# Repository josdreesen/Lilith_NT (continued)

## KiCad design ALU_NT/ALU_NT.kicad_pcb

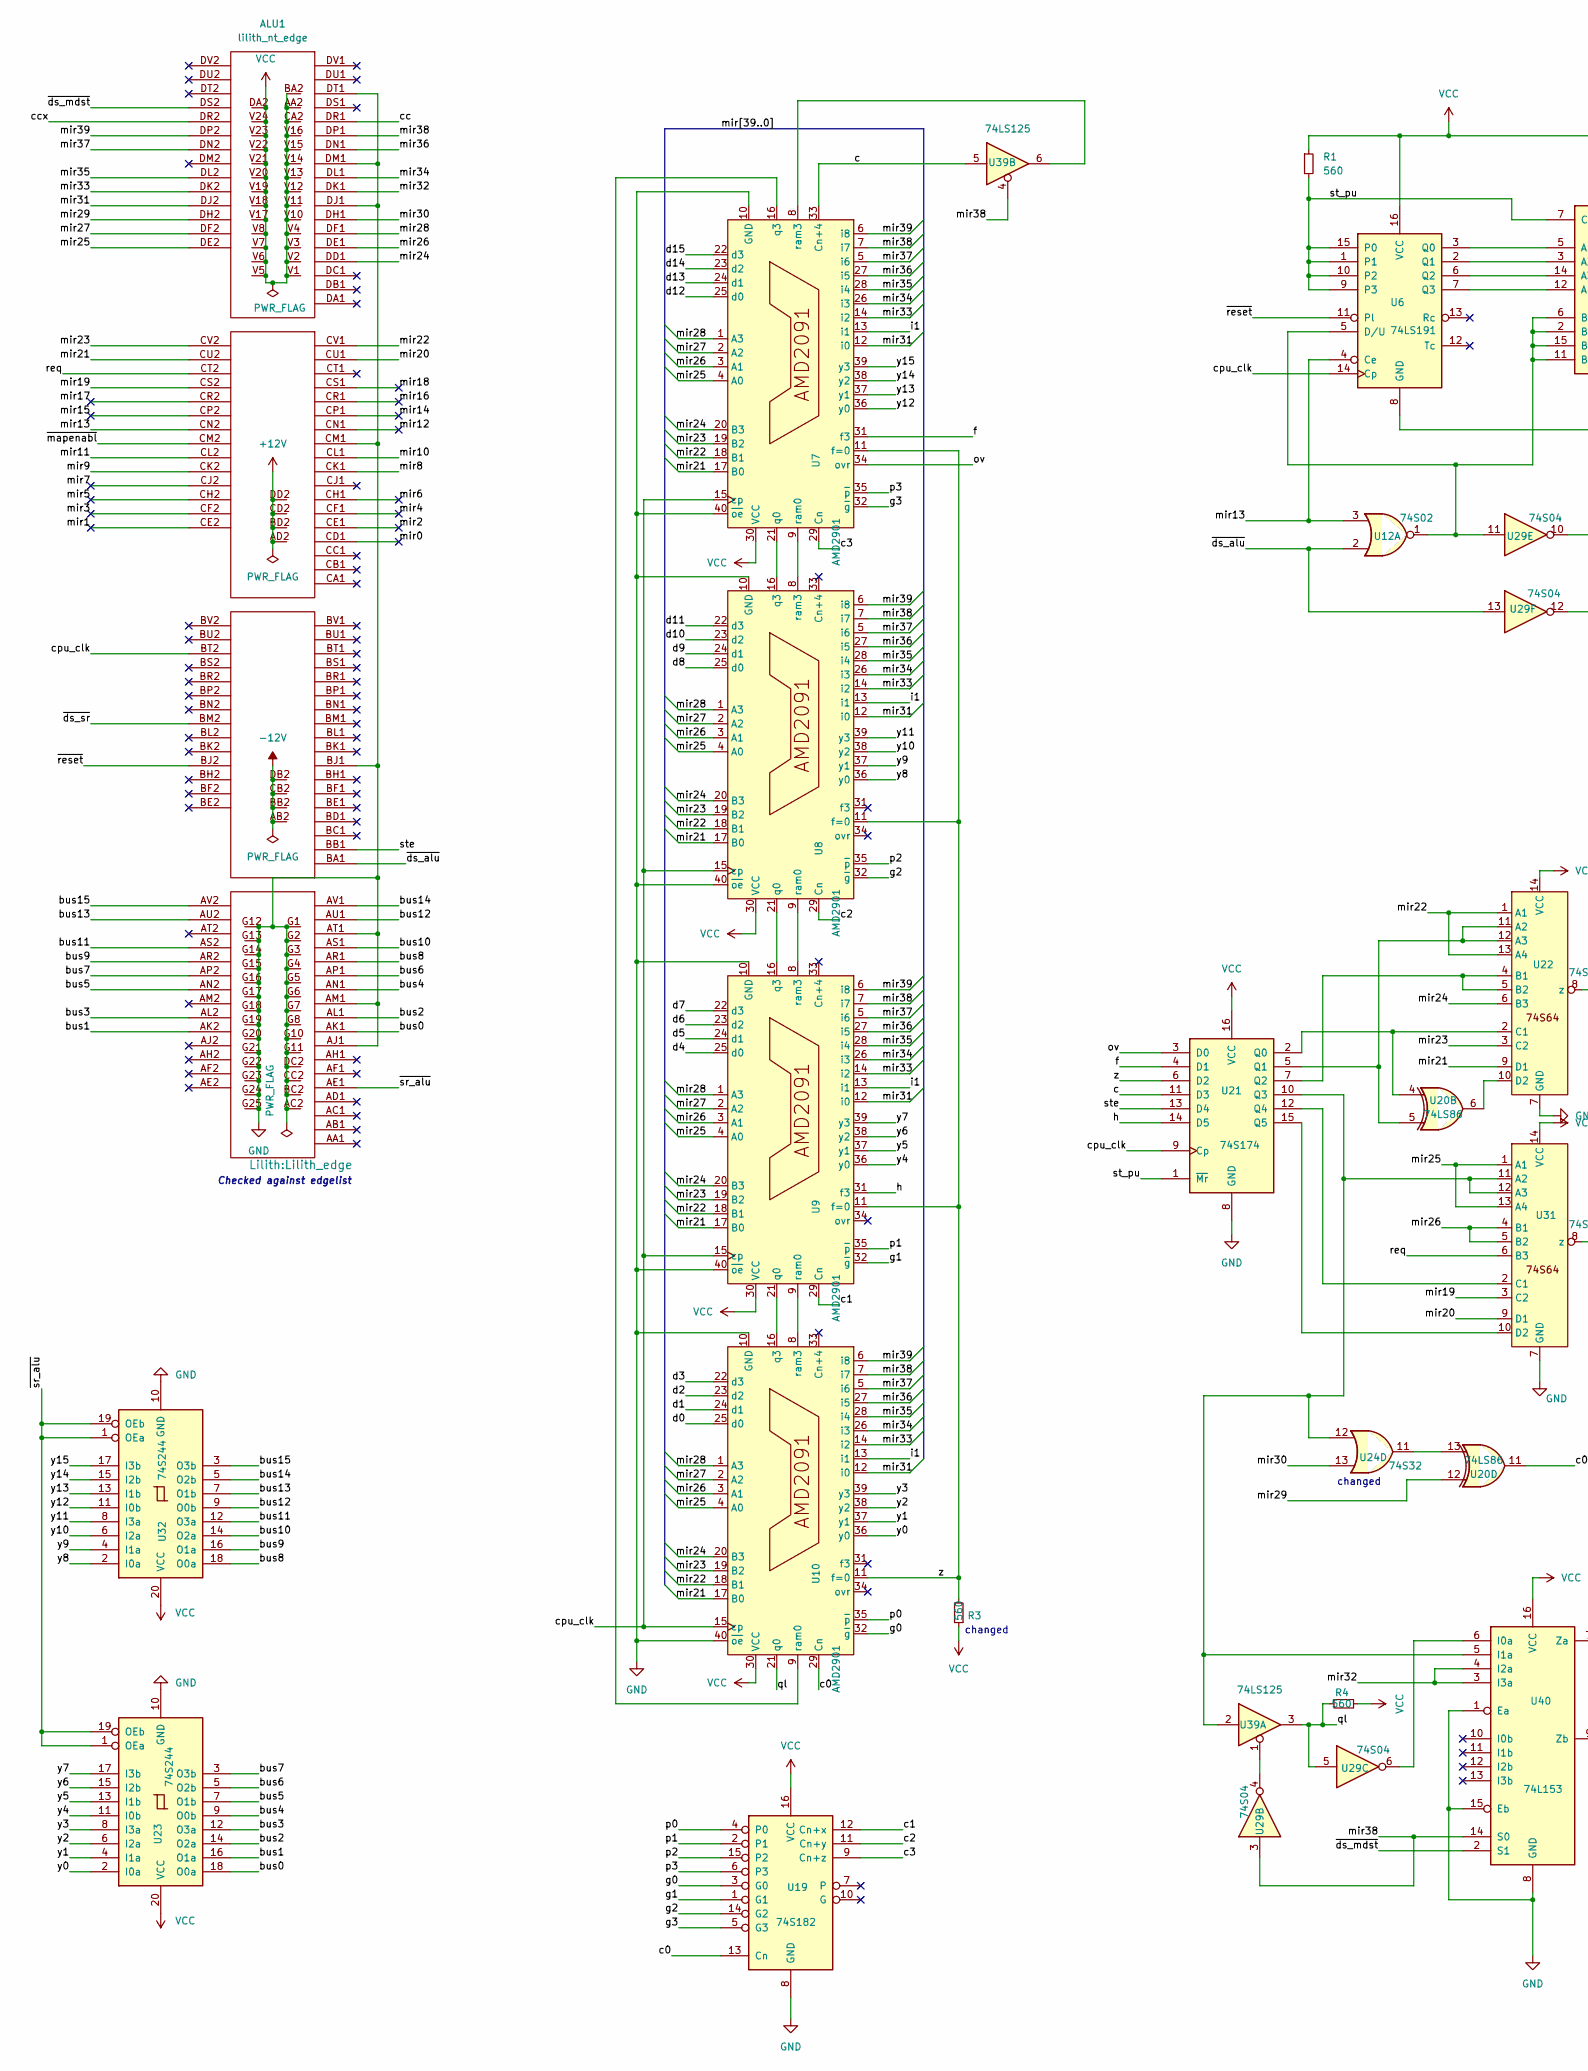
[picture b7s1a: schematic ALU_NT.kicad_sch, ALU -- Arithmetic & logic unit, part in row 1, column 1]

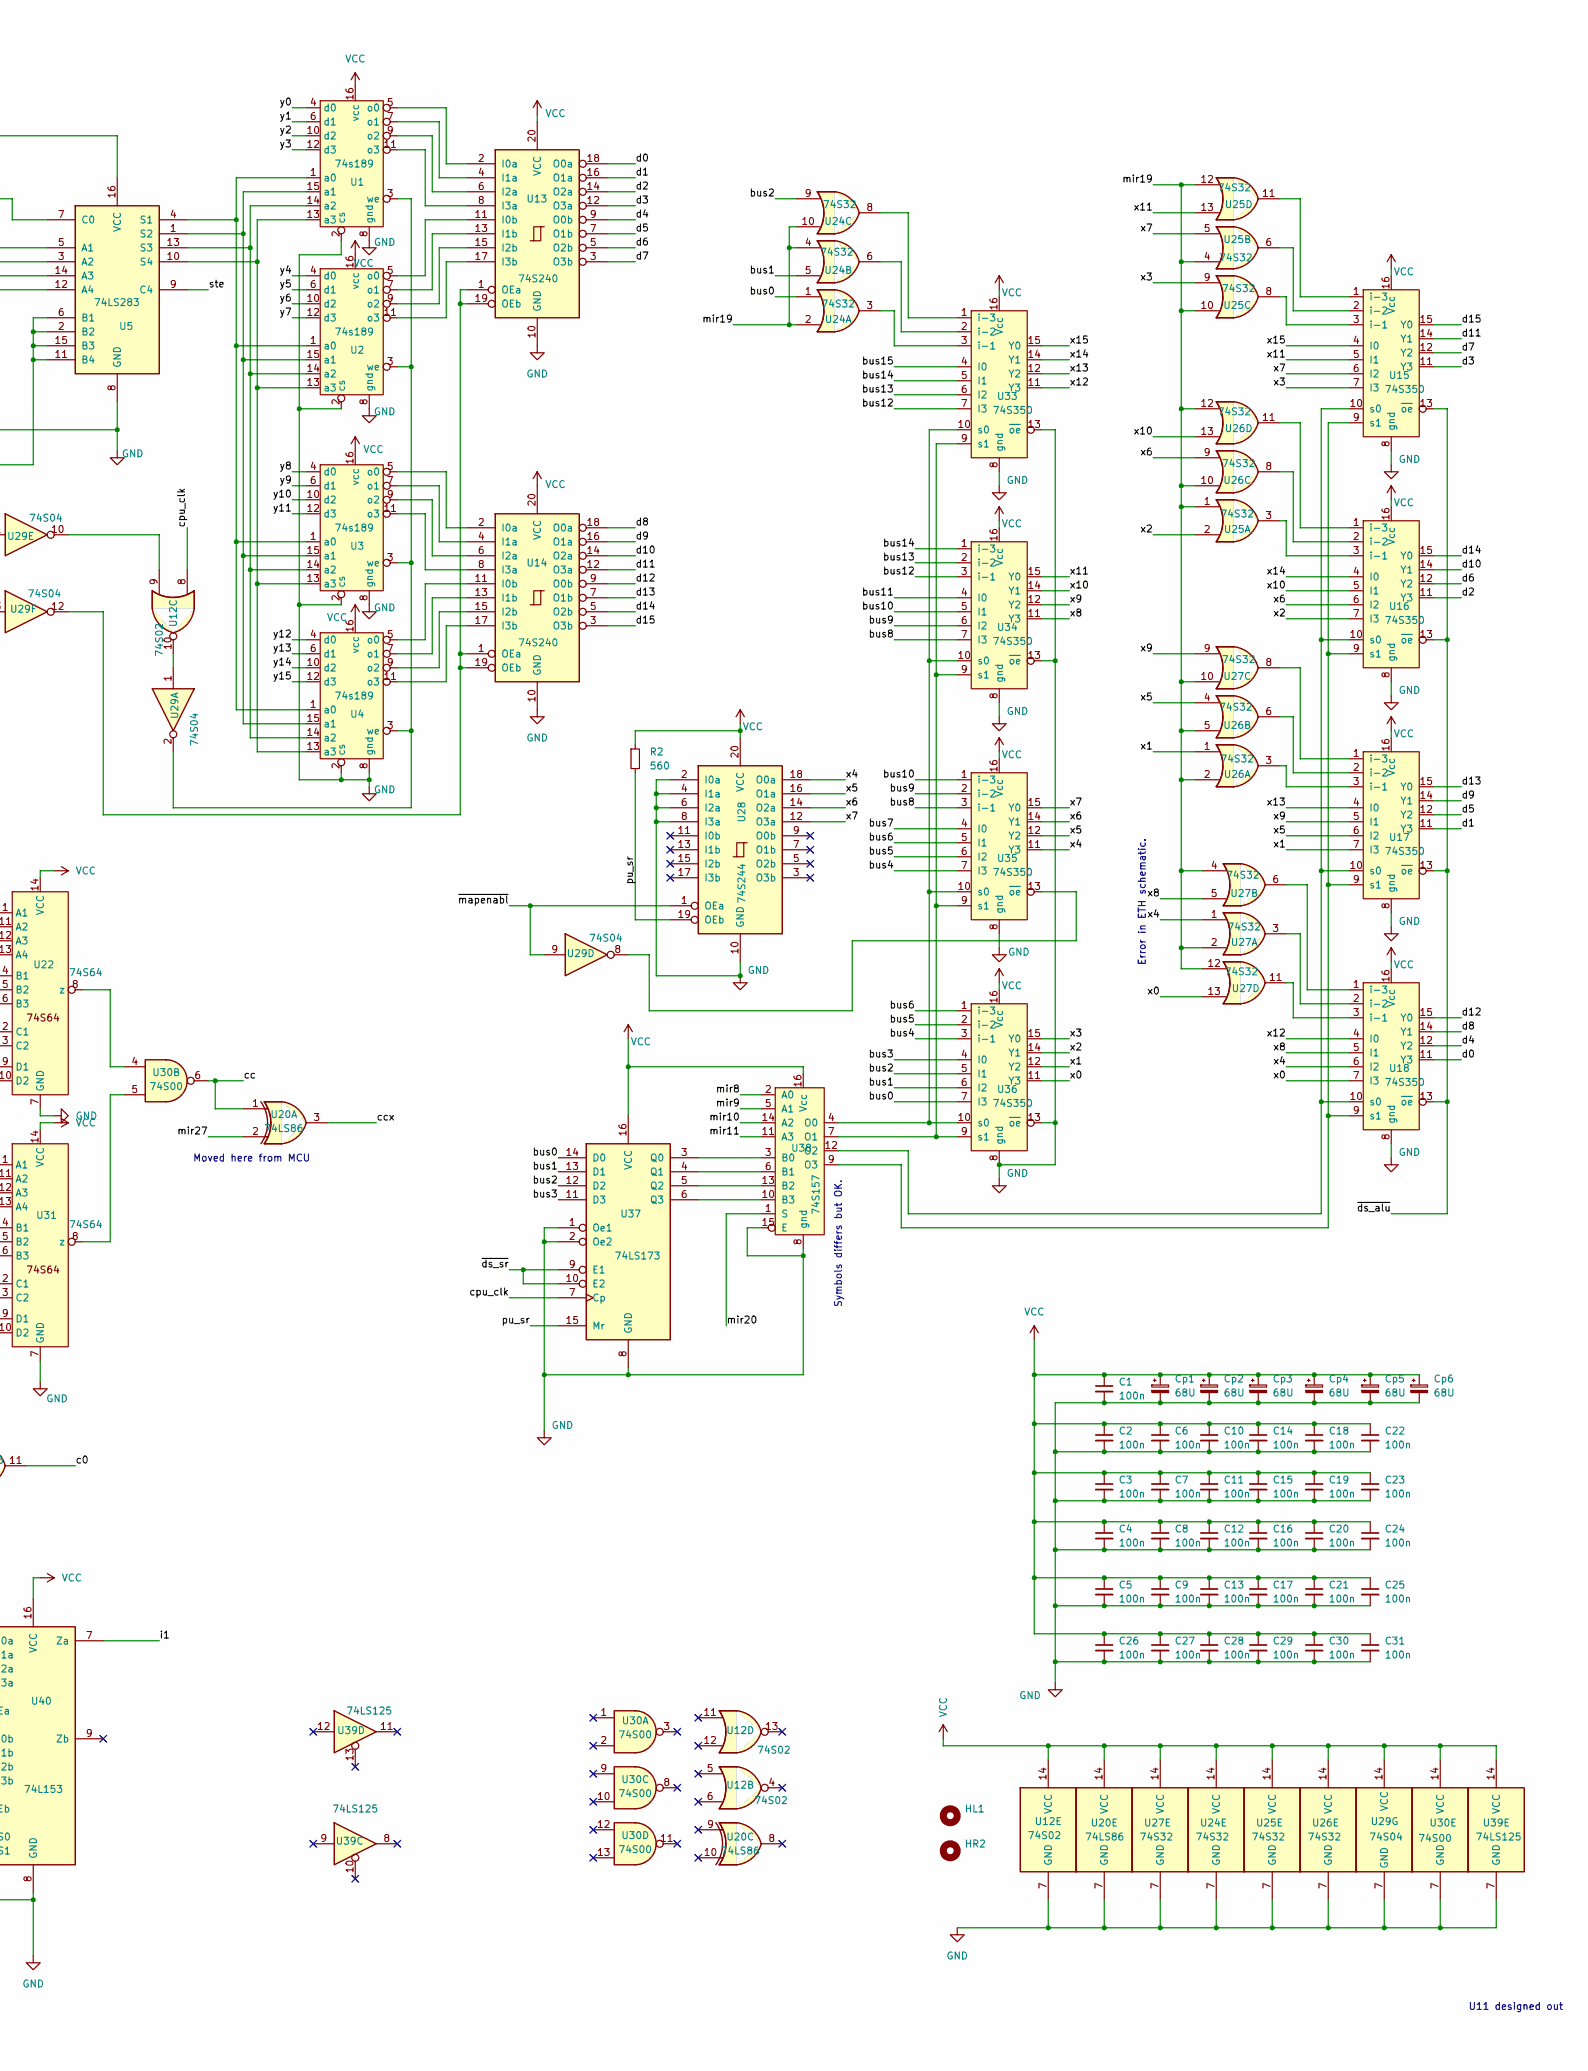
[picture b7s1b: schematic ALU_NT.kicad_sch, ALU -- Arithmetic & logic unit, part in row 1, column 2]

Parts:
ALU1: lilith_nt_edge; Lilith_edge
C1, C2, C3, C4, C5, C6, C7, C8, C9, C10, C11, C12, C13, C14, C15, C16, C17, C18, C19, C20, C21, C22, C23, C24, C25, C26, C27, C28, C29, C30, C31: 100n; C_1206_3216Metric_Pad1.33x1.80mm_HandSolder
Cp1, Cp2, Cp3, Cp4, Cp5, Cp6: 68U; CP_PHP
HL1: MountingHole; Handle
HR2: MountingHole; Handle
R1, R2, R3, R4: 560; R_Axial_DIN0204_L3.6mm_D1.6mm_P7.62mm_Horizontal
U1, U2, U3, U4: 74s189; DIP-16_W7.62mm
U5: 74LS283; DIP-16_W7.62mm
U6: 74LS191; DIP-16_W7.62mm
U7, U8, U9, U10: AMD2901; DIP-40_W15.24mm
U12: 74S02; DIP-14_W7.62mm
U13, U14: 74S240; DIP-20_W7.62mm
U15, U16, U17, U18, U33, U34, U35, U36: 74S350; DIP-16_W7.62mm
U19: 74S182; DIP-16_W7.62mm
U20: 74LS86; DIP-14_W7.62mm
U21: 74S174; DIP-16_W7.62mm
U22, U31: 74S64; DIP-14_W7.62mm
U23, U28, U32: 74S244; DIP-20_W7.62mm
U24, U25, U26, U27: 74S32; DIP-14_W7.62mm
U29: 74S04; DIP-14_W7.62mm
U30: 74S00; DIP-14_W7.62mm
U37: 74LS173; DIP-16_W7.62mm
U38: 74S157; DIP-16_W7.62mm
U39: 74LS125; DIP-14_W7.62mm
U40: 74L153; DIP-16_W7.62mm

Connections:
+12V: ALU1.AD2, ALU1.BD2, ALU1.CD2, ALU1.DD2
-12V: ALU1.AB2, ALU1.BB2, ALU1.CB2, ALU1.DB2
/bus0: ALU1.AK1, U23.18 (O0a), U24.1, U36.7 (I3), U37.14 (D0)
/bus1: ALU1.AK2, U23.16 (O1a), U24.5, U36.6 (I2), U37.13 (D1)
/bus2: ALU1.AL1, U23.14 (O2a), U24.9, U36.5 (I1), U37.12 (D2)
/bus3: ALU1.AL2, U23.12 (O3a), U36.4 (I0), U37.11 (D3)
/bus4: ALU1.AN1, U23.9 (O0b), U35.7 (I3), U36.3 (i-1)
/bus5: ALU1.AN2, U23.7 (O1b), U35.6 (I2), U36.2 (i-2)
/bus6: ALU1.AP1, U23.5 (O2b), U35.5 (I1), U36.1 (i-3)
/bus7: ALU1.AP2, U23.3 (O3b), U35.4 (I0)
/bus8: ALU1.AR1, U32.18 (O0a), U34.7 (I3), U35.3 (i-1)
/bus9: ALU1.AR2, U32.16 (O1a), U34.6 (I2), U35.2 (i-2)
/bus10: ALU1.AS1, U32.14 (O2a), U34.5 (I1), U35.1 (i-3)
/bus11: ALU1.AS2, U32.12 (O3a), U34.4 (I0)
/bus12: ALU1.AU1, U32.9 (O0b), U33.7 (I3), U34.3 (i-1)
/bus13: ALU1.AU2, U32.7 (O1b), U33.6 (I2), U34.2 (i-2)
/bus14: ALU1.AV1, U32.5 (O2b), U33.5 (I1), U34.1 (i-3)
/bus15: ALU1.AV2, U32.3 (O3b), U33.4 (I0)
/c: U7.33 (Cn+4), U21.11 (D3), U39.5
/c0: U10.29 (Cn), U19.13 (Cn), U20.11
/c1: U9.29 (Cn), U19.12 (Cn+x)
/c2: U8.29 (Cn), U19.11 (Cn+y)
/c3: U7.29 (Cn), U19.9 (Cn+z)
/cc: ALU1.DR1, U20.1, U30.6
/ccx: ALU1.DR2, U20.3
/cpu_clk: ALU1.BT2, U6.14 (Cp), U7.15 (cp), U8.15 (cp), U9.15 (cp), U10.15 (cp), U12.8, U21.9 (Cp), U37.7 (Cp)
/d0: U10.25 (d0), U13.18 (O0a), U18.11 (Y3)
/d1: U10.24 (d1), U13.16 (O1a), U17.11 (Y3)
/d2: U10.23 (d2), U13.14 (O2a), U16.11 (Y3)
/d3: U10.22 (d3), U13.12 (O3a), U15.11 (Y3)
/d4: U9.25 (d0), U13.9 (O0b), U18.12 (Y2)
/d5: U9.24 (d1), U13.7 (O1b), U17.12 (Y2)
/d6: U9.23 (d2), U13.5 (O2b), U16.12 (Y2)
/d7: U9.22 (d3), U13.3 (O3b), U15.12 (Y2)
/d8: U8.25 (d0), U14.18 (O0a), U18.14 (Y1)
/d9: U8.24 (d1), U14.16 (O1a), U17.14 (Y1)
/d10: U8.23 (d2), U14.14 (O2a), U16.14 (Y1)
/d11: U8.22 (d3), U14.12 (O3a), U15.14 (Y1)
/d12: U7.25 (d0), U14.9 (O0b), U18.15 (Y0)
/d13: U7.24 (d1), U14.7 (O1b), U17.15 (Y0)
/d14: U7.23 (d2), U14.5 (O2b), U16.15 (Y0)
/d15: U7.22 (d3), U14.3 (O3b), U15.15 (Y0)
/f: U7.31 (f3), U21.4 (D1)
/g0: U10.32 (~g), U19.3 (G0)
/g1: U9.32 (~g), U19.1 (G1)
/g2: U8.32 (~g), U19.14 (G2)
/g3: U7.32 (~g), U19.5 (G3)
/h: U9.31 (f3), U21.14 (D5)
/i1: U7.13 (i1), U8.13 (i1), U9.13 (i1), U10.13 (i1), U40.7 (Za)
/mir0: ALU1.CD1
/mir1: ALU1.CE2
/mir2: ALU1.CE1
/mir3: ALU1.CF2
/mir4: ALU1.CF1
/mir5: ALU1.CH2
/mir6: ALU1.CH1
/mir7: ALU1.CJ2
/mir8: ALU1.CK1, U38.2 (A0)
/mir9: ALU1.CK2, U38.5 (A1)
/mir10: ALU1.CL1, U38.14 (A2)
/mir11: ALU1.CL2, U38.11 (A3)
/mir12: ALU1.CN1
/mir13: ALU1.CN2, U6.4 (Ce), U12.3
/mir14: ALU1.CP1
/mir15: ALU1.CP2
/mir16: ALU1.CR1
/mir17: ALU1.CR2
/mir18: ALU1.CS1
/mir19: ALU1.CS2, U24.2, U24.4, U24.10, U25.1, U25.4, U25.10, U25.12, U26.2, U26.5, U26.10, U26.12, U27.2, U27.4, U27.10, U27.12, U31.3 (C2)
/mir20: ALU1.CU1, U31.9 (D1), U38.1 (S)
/mir21: ALU1.CU2, U7.17 (B0), U8.17 (B0), U9.17 (B0), U10.17 (B0), U22.9 (D1)
/mir22: ALU1.CV1, U7.18 (B1), U8.18 (B1), U9.18 (B1), U10.18 (B1), U22.1 (A1), U22.13 (A4)
/mir23: ALU1.CV2, U7.19 (B2), U8.19 (B2), U9.19 (B2), U10.19 (B2), U22.3 (C2)
/mir24: ALU1.DD1, U7.20 (B3), U8.20 (B3), U9.20 (B3), U10.20 (B3), U22.6 (B3)
/mir25: ALU1.DE2, U7.4 (A0), U8.4 (A0), U9.4 (A0), U10.4 (A0), U31.1 (A1), U31.13 (A4)
/mir26: ALU1.DE1, U7.3 (A1), U8.3 (A1), U9.3 (A1), U10.3 (A1), U31.4 (B1), U31.5 (B2)
/mir27: ALU1.DF2, U7.2 (A2), U8.2 (A2), U9.2 (A2), U10.2 (A2), U20.2
/mir28: ALU1.DF1, U7.1 (A3), U8.1 (A3), U9.1 (A3), U10.1 (A3)
/mir29: ALU1.DH2, U20.12
/mir30: ALU1.DH1, U24.13
/mir31: ALU1.DJ2, U7.12 (i0), U8.12 (i0), U9.12 (i0), U10.12 (i0)
/mir32: ALU1.DK1, U40.3 (I3a), U40.4 (I2a)
/mir33: ALU1.DK2, U7.14 (i2), U8.14 (i2), U9.14 (i2), U10.14 (i2)
/mir34: ALU1.DL1, U7.26 (i3), U8.26 (i3), U9.26 (i3), U10.26 (i3)
/mir35: ALU1.DL2, U7.28 (i4), U8.28 (i4), U9.28 (i4), U10.28 (i4)
/mir36: ALU1.DN1, U7.27 (i5), U8.27 (i5), U9.27 (i5), U10.27 (i5)
/mir37: ALU1.DN2, U7.5 (i6), U8.5 (i6), U9.5 (i6), U10.5 (i6)
/mir38: ALU1.DP1, U7.7 (i7), U8.7 (i7), U9.7 (i7), U10.7 (i7), U29.3, U39.4, U40.14 (S0)
/mir39: ALU1.DP2, U7.6 (i8), U8.6 (i8), U9.6 (i8), U10.6 (i8)
/ov: U7.34 (ovr), U21.3 (D0)
/p0: U10.35 (~p), U19.4 (P0)
/p1: U9.35 (~p), U19.2 (P1)
/p2: U8.35 (~p), U19.15 (P2)
/p3: U7.35 (~p), U19.6 (P3)
/pu_sr: R2.2, U28.19 (OEb), U37.15 (Mr)
/ql: R4.2, U10.21 (q0), U29.5, U39.3
/req: ALU1.CT2, U31.6 (B3)
/st_pu: R1.2, U5.7 (C0), U6.1, U6.9 (P3), U6.10 (P2), U6.15 (P0), U21.1 (~Mr)
/ste: ALU1.BB1, U5.9 (C4), U21.13 (D4)
/x0: U18.7 (I3), U27.13, U36.11 (Y3)
/x1: U17.7 (I3), U26.1, U36.12 (Y2)
/x2: U16.7 (I3), U25.2, U36.14 (Y1)
/x3: U15.7 (I3), U25.9, U36.15 (Y0)
/x4: U18.6 (I2), U27.1, U28.18 (O0a), U35.11 (Y3)
/x5: U17.6 (I2), U26.4, U28.16 (O1a), U35.12 (Y2)
/x6: U16.6 (I2), U26.9, U28.14 (O2a), U35.14 (Y1)
/x7: U15.6 (I2), U25.5, U28.12 (O3a), U35.15 (Y0)
/x8: U18.5 (I1), U27.5, U34.11 (Y3)
/x9: U17.5 (I1), U27.9, U34.12 (Y2)
/x10: U16.5 (I1), U26.13, U34.14 (Y1)
/x11: U15.5 (I1), U25.13, U34.15 (Y0)
/x12: U18.4 (I0), U33.11 (Y3)
/x13: U17.4 (I0), U33.12 (Y2)
/x14: U16.4 (I0), U33.14 (Y1)
/x15: U15.4 (I0), U33.15 (Y0)
/y0: U1.4 (d0), U10.36 (y0), U23.2 (I0a)
/y1: U1.6 (d1), U10.37 (y1), U23.4 (I1a)
/y2: U1.10 (d2), U10.38 (y2), U23.6 (I2a)
/y3: U1.12 (d3), U10.39 (y3), U23.8 (I3a)
/y4: U2.4 (d0), U9.36 (y0), U23.11 (I0b)
/y5: U2.6 (d1), U9.37 (y1), U23.13 (I1b)
/y6: U2.10 (d2), U9.38 (y2), U23.15 (I2b)
/y7: U2.12 (d3), U9.39 (y3), U23.17 (I3b)
/y8: U3.4 (d0), U8.36 (y0), U32.2 (I0a)
/y9: U3.6 (d1), U8.37 (y1), U32.4 (I1a)
/y10: U3.10 (d2), U8.38 (y2), U32.6 (I2a)
/y11: U3.12 (d3), U8.39 (y3), U32.8 (I3a)
/y12: U4.4 (d0), U7.36 (y0), U32.11 (I0b)
/y13: U4.6 (d1), U7.37 (y1), U32.13 (I1b)
/y14: U4.10 (d2), U7.38 (y2), U32.15 (I2b)
/y15: U4.12 (d3), U7.39 (y3), U32.17 (I3b)
/z: R3.2, U7.11 (f=0), U8.11 (f=0), U9.11 (f=0), U10.11 (f=0), U21.6 (D2)
/~ds_alu: ALU1.BA1, U12.2, U15.13 (~oe), U16.13 (~oe), U17.13 (~oe), U18.13 (~oe), U29.13
/~ds_mdst: ALU1.DS2, U40.2 (S1)
/~ds_sr: ALU1.BM2, U37.9 (E1), U37.10 (E2)
/~mapenabl: ALU1.CM2, U28.1 (OEa), U29.9
/~reset: ALU1.BJ2, U6.11 (Pl)
/~sr_alu: ALU1.AE1, U23.1 (OEa), U23.19 (OEb), U32.1 (OEa), U32.19 (OEb)
GND: ALU1.AC2, ALU1.AJ1, ALU1.AM1, ALU1.AT1, ALU1.BC2, ALU1.BJ1, ALU1.CC2, ALU1.CM1, ALU1.DC2, ALU1.DJ1, ALU1.DM1, ALU1.DT1, ALU1.G1 (GND), ALU1.G2 (GND), ALU1.G3 (GND), ALU1.G4 (GND), ALU1.G5 (GND), ALU1.G6 (GND), ALU1.G7 (GND), ALU1.G8 (GND), ALU1.G10, ALU1.G11, ALU1.G12, ALU1.G13, ALU1.G14, ALU1.G15, ALU1.G16, ALU1.G17, ALU1.G18, ALU1.G19, ALU1.G20, ALU1.G21, ALU1.G22, ALU1.G23, ALU1.G24, ALU1.G25, C1.2, C2.2, C3.2, C4.2, C5.2, C6.2, C7.2, C8.2, C9.2, C10.2, C11.2, C12.2, C13.2, C14.2, C15.2, C16.2, C17.2, C18.2, C19.2, C20.2, C21.2, C22.2, C23.2, C24.2, C25.2, C26.2, C27.2, C28.2, C29.2, C30.2, C31.2, Cp1.2, Cp2.2, Cp3.2, Cp4.2, Cp5.2, Cp6.2, U1.2 (cs), U1.8 (gnd), U2.2 (cs), U2.8 (gnd), U3.2 (cs), U3.8 (gnd), U4.2 (cs), U4.8 (gnd), U5.8 (GND), U6.8 (GND), U7.10 (GND), U7.40 (~oe), U8.10 (GND), U8.40 (~oe), U9.10 (GND), U9.40 (~oe), U10.10 (GND), U10.40 (~oe), U12.7 (GND), U13.10 (GND), U14.10 (GND), U15.8 (gnd), U16.8 (gnd), U17.8 (gnd), U18.8 (gnd), U19.8 (GND), U20.7 (GND), U21.8 (GND), U22.7 (GND), U23.10 (GND), U24.7 (GND), U25.7 (GND), U26.7 (GND), U27.7 (GND), U28.2 (I0a), U28.4 (I1a), U28.6 (I2a), U28.8 (I3a), U28.10 (GND), U29.7 (GND), U30.7 (GND), U31.7 (GND), U32.10 (GND), U33.8 (gnd), U33.13 (~oe), U34.8 (gnd), U34.13 (~oe), U35.8 (gnd), U36.8 (gnd), U36.13 (~oe), U37.1 (Oe1), U37.2 (Oe2), U37.8 (GND), U38.8 (gnd), U38.15 (E), U39.7 (GND), U40.1 (Ea), U40.8 (GND), U40.15 (Eb)
unnamed: U1.1 (a0), U2.1 (a0), U3.1 (a0), U4.1 (a0), U5.4 (S1)
unnamed: U1.15 (a1), U2.15 (a1), U3.15 (a1), U4.15 (a1), U5.1 (S2)
unnamed: U1.14 (a2), U2.14 (a2), U3.14 (a2), U4.14 (a2), U5.13 (S3)
unnamed: U1.13 (a3), U2.13 (a3), U3.13 (a3), U4.13 (a3), U5.10 (S4)
unnamed: U1.5 (o0), U13.2 (I0a)
unnamed: U1.7 (o1), U13.4 (I1a)
unnamed: U1.9 (o2), U13.6 (I2a)
unnamed: U1.11 (o3), U13.8 (I3a)
unnamed: U1.3 (we), U2.3 (we), U3.3 (we), U4.3 (we), U29.2
unnamed: U5.5 (A1), U6.3 (Q0)
unnamed: U5.3 (A2), U6.2 (Q1)
unnamed: U5.14 (A3), U6.6 (Q2)
unnamed: U5.12 (A4), U6.7 (Q3)
unnamed: U5.2 (B2), U5.6 (B1), U5.11 (B4), U5.15 (B3), U6.5 (D/U), U12.1, U29.11
unnamed: U7.21 (q0), U8.16 (q3)
unnamed: U7.9 (ram0), U8.8 (ram3)
unnamed: U7.8 (ram3), U39.6
unnamed: U8.21 (q0), U9.16 (q3)
unnamed: U8.9 (ram0), U9.8 (ram3)
unnamed: U9.21 (q0), U10.16 (q3)
unnamed: U7.16 (q3), U10.9 (ram0)
unnamed: U9.9 (ram0), U10.8 (ram3)
unnamed: U12.9, U29.10
unnamed: U12.10, U29.1
unnamed: U2.5 (o0), U13.11 (I0b)
unnamed: U2.7 (o1), U13.13 (I1b)
unnamed: U2.9 (o2), U13.15 (I2b)
unnamed: U2.11 (o3), U13.17 (I3b)
unnamed: U13.1 (OEa), U13.19 (OEb), U14.1 (OEa), U14.19 (OEb), U29.12
unnamed: U3.5 (o0), U14.2 (I0a)
unnamed: U4.5 (o0), U14.11 (I0b)
unnamed: U3.7 (o1), U14.4 (I1a)
unnamed: U4.7 (o1), U14.13 (I1b)
unnamed: U3.9 (o2), U14.6 (I2a)
unnamed: U4.9 (o2), U14.15 (I2b)
unnamed: U3.11 (o3), U14.8 (I3a)
unnamed: U4.11 (o3), U14.17 (I3b)
unnamed: U15.3 (i-1), U25.8
unnamed: U15.2 (i-2), U25.6
unnamed: U15.1 (i-3), U25.11
unnamed: U15.10 (s0), U16.10 (s0), U17.10 (s0), U18.10 (s0), U38.12 (O2)
unnamed: U15.9 (s1), U16.9 (s1), U17.9 (s1), U18.9 (s1), U38.9 (O3)
unnamed: U16.3 (i-1), U25.3
unnamed: U16.2 (i-2), U26.8
unnamed: U16.1 (i-3), U26.11
unnamed: U17.3 (i-1), U26.3
unnamed: U17.2 (i-2), U26.6
unnamed: U17.1 (i-3), U27.8
unnamed: U18.3 (i-1), U27.11
unnamed: U18.2 (i-2), U27.3
unnamed: U18.1 (i-3), U27.6
unnamed: U20.13, U24.11
unnamed: U20.4, U21.2 (Q0), U22.2 (C1)
unnamed: U20.5, U21.5 (Q1), U22.11 (A2), U22.12 (A3)
unnamed: U21.7 (Q2), U22.4 (B1), U22.5 (B2)
unnamed: U21.10 (Q3), U24.12, U31.11 (A2), U31.12 (A3), U39.2, U40.5 (I1a)
unnamed: U21.12 (Q4), U31.2 (C1)
unnamed: U21.15 (Q5), U31.10 (D2)
unnamed: U20.6, U22.10 (D2)
unnamed: U22.8 (z), U30.4
unnamed: U29.4, U39.1
unnamed: U30.5, U31.8 (z)
unnamed: U24.3, U33.3 (i-1)
unnamed: U24.6, U33.2 (i-2)
unnamed: U24.8, U33.1 (i-3)
unnamed: U33.10 (s0), U34.10 (s0), U35.10 (s0), U36.10 (s0), U38.4 (O0)
unnamed: U33.9 (s1), U34.9 (s1), U35.9 (s1), U36.9 (s1), U38.7 (O1)
unnamed: U29.8, U35.13 (~oe)
unnamed: U37.3 (Q0), U38.3 (B0)
unnamed: U37.4 (Q1), U38.6 (B1)
unnamed: U37.5 (Q2), U38.13 (B2)
unnamed: U37.6 (Q3), U38.10 (B3)
unnamed: U29.6, U40.6 (I0a)
VCC: ALU1.AA2, ALU1.BA2, ALU1.CA2, ALU1.DA2, ALU1.V1 (VCC), ALU1.V2 (VCC), ALU1.V3 (VCC), ALU1.V4 (VCC), ALU1.V5 (VCC), ALU1.V6 (VCC), ALU1.V7 (VCC), ALU1.V8 (VCC), ALU1.V10, ALU1.V11, ALU1.V12, ALU1.V13, ALU1.V14, ALU1.V15, ALU1.V16, ALU1.V17, ALU1.V18, ALU1.V19, ALU1.V20, ALU1.V21, ALU1.V22, ALU1.V23, ALU1.V24, C1.1, C2.1, C3.1, C4.1, C5.1, C6.1, C7.1, C8.1, C9.1, C10.1, C11.1, C12.1, C13.1, C14.1, C15.1, C16.1, C17.1, C18.1, C19.1, C20.1, C21.1, C22.1, C23.1, C24.1, C25.1, C26.1, C27.1, C28.1, C29.1, C30.1, C31.1, Cp1.1, Cp2.1, Cp3.1, Cp4.1, Cp5.1, Cp6.1, R1.1, R2.1, R3.1, R4.1, U1.16 (vcc), U2.16 (vcc), U3.16 (vcc), U4.16 (vcc), U5.16 (VCC), U6.16 (VCC), U7.30 (VCC), U8.30 (VCC), U9.30 (VCC), U10.30 (VCC), U12.14 (VCC), U13.20 (VCC), U14.20 (VCC), U15.16 (Vcc), U16.16 (Vcc), U17.16 (Vcc), U18.16 (Vcc), U19.16 (VCC), U20.14 (VCC), U21.16 (VCC), U22.14 (VCC), U23.20 (VCC), U24.14 (VCC), U25.14 (VCC), U26.14 (VCC), U27.14 (VCC), U28.20 (VCC), U29.14 (VCC), U30.14 (VCC), U31.14 (VCC), U32.20 (VCC), U33.16 (Vcc), U34.16 (Vcc), U35.16 (Vcc), U36.16 (Vcc), U37.16 (VCC), U38.16 (Vcc), U39.14 (VCC), U40.16 (VCC)

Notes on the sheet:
changed
Error in ETH schematic.
Checked against edgelist
Symbols differs but OK.
U11 designed out
Moved here from MCU

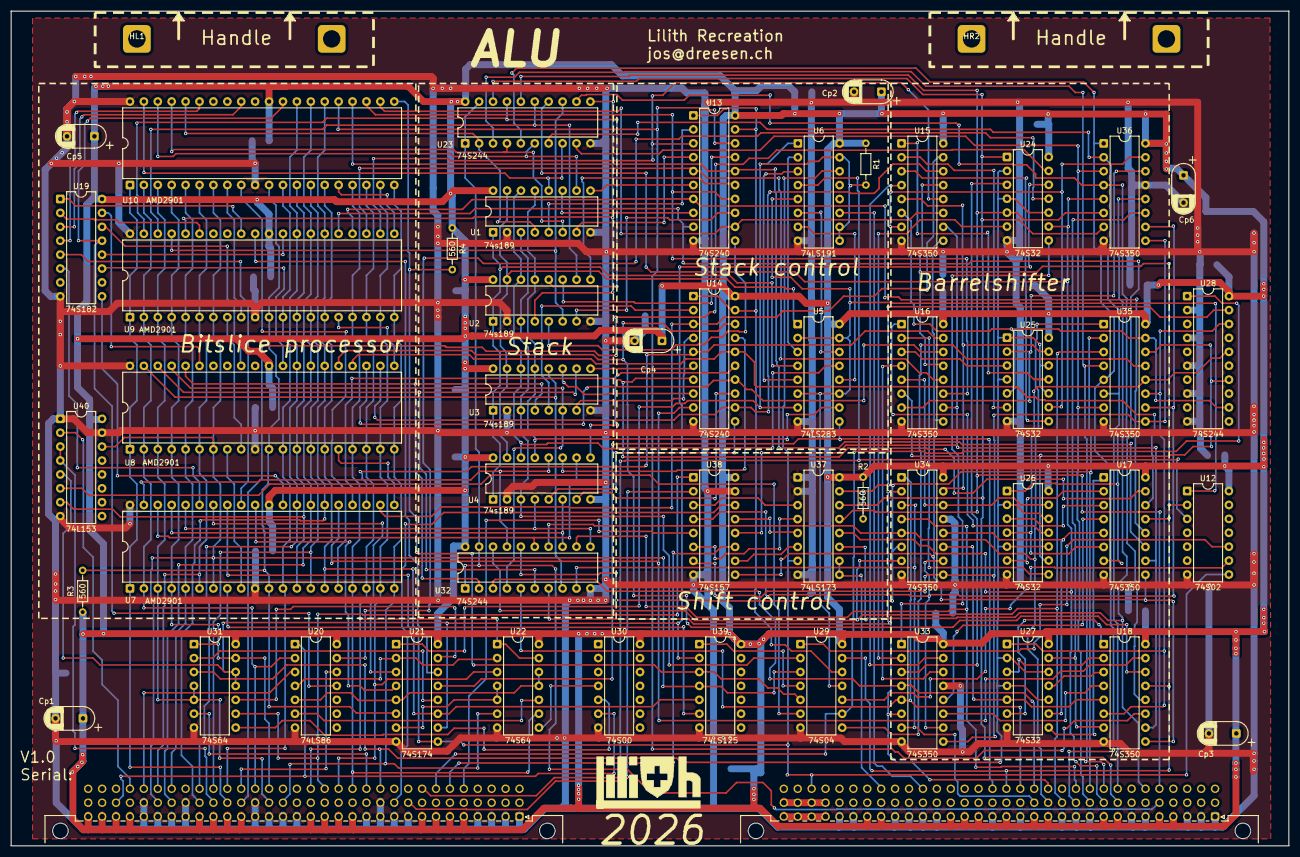
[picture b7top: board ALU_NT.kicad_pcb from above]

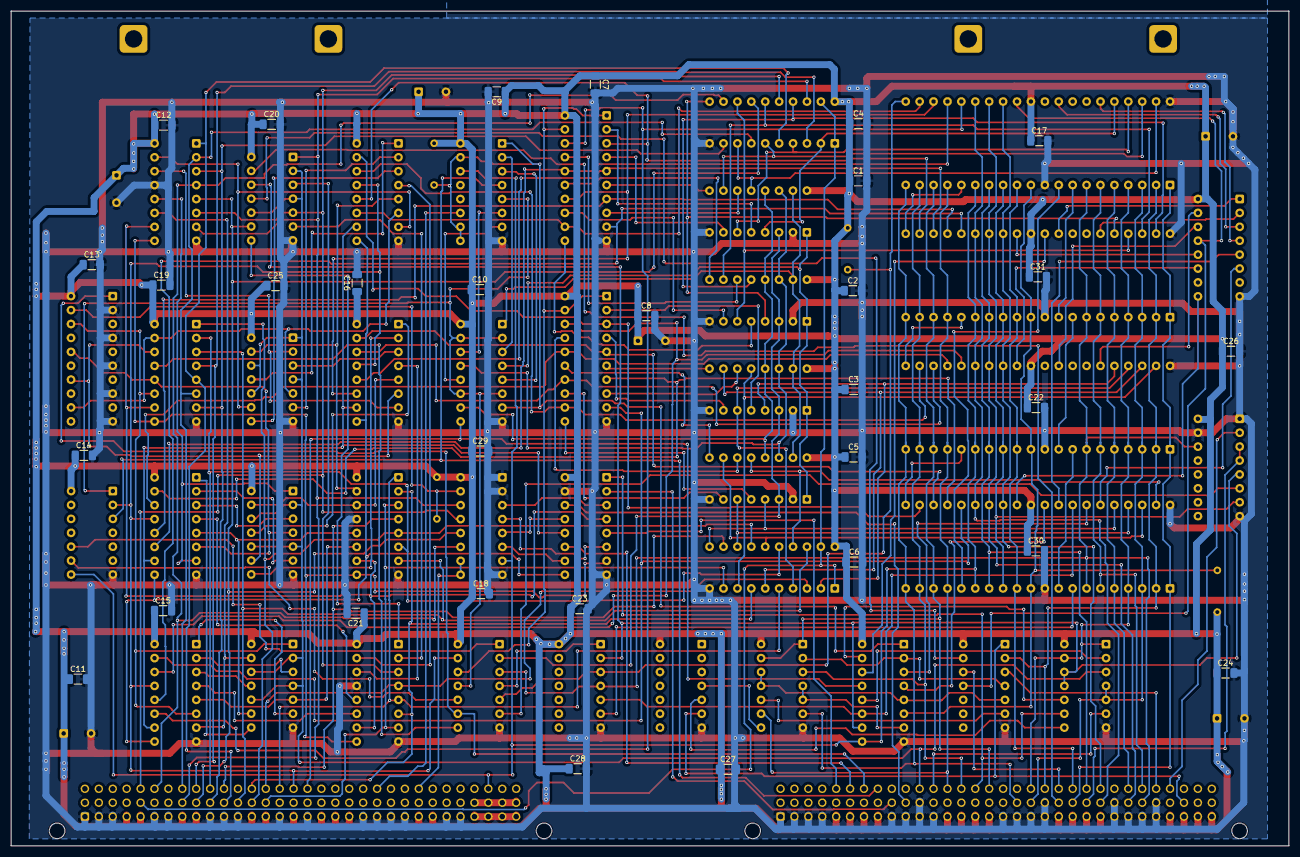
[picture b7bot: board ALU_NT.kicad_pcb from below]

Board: 2 copper layers, 233.3 x 152.4 mm, 83 parts (31 on the bottom side), 199 nets.

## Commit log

2026-03-04 First README.md
2026-03-06 README.md typo's removed
2026-03-21 correct files for the DSP unit.
2026-03-22 Delete DSP_NT/DRAM_NT.jpg
    File wa in wrong directtory
2026-03-22 First release for newly finished IO block
2026-03-31 V1.0 release
    First release, corresponds to first version of PCB's
2026-03-31 V1.0 release
    This release corresponds to V1.0 release of the PCB.
2026-03-31 Release V1.0
    This release corresponds to V1.0 release of the PCB.
